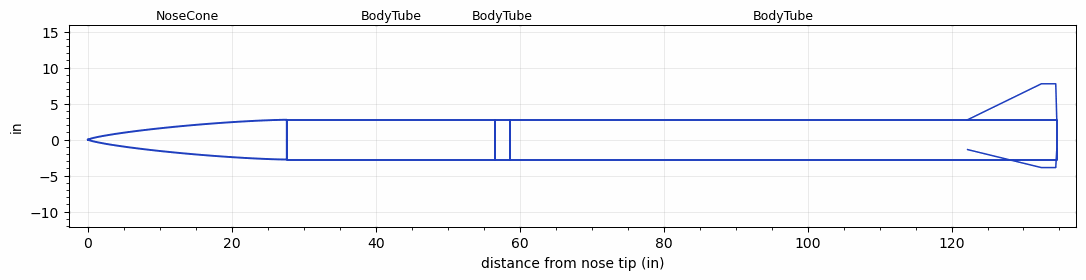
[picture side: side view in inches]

<RASAeroDocument>
 <FileVersion>2</FileVersion>
 <RocketDesign>
  <NoseCone>
   <Length>27.6249</Length>
   <Diameter>5.525</Diameter>
   <Shape>Von Karman Ogive</Shape>
   <Location>0</Location>
  </NoseCone>
  <BodyTube>
   <Length>28.9999</Length>
   <Diameter>5.525</Diameter>
   <Location>27.6249</Location>
  </BodyTube>
  <BodyTube>
   <Length>2</Length>
   <Diameter>5.525</Diameter>
   <Location>56.6249</Location>
  </BodyTube>
  <BodyTube>
   <Length>75.9998</Length>
   <Diameter>5.525</Diameter>
   <Location>58.6249</Location>
   <Fin>
    <Count>3</Count>
    <Chord>12.3937</Chord>
    <Span>5</Span>
    <SweepDistance>10.2515</SweepDistance>
    <TipChord>2</TipChord>
    <Thickness>0.25</Thickness>
    <Location>12.3937</Location>
    <AirfoilSection>Subsonic NACA</AirfoilSection>
   </Fin>
  </BodyTube>
  <Surface>Camouflage Paint</Surface>
  <ModifiedBarrowman>False</ModifiedBarrowman>
  <Turbulence>False</Turbulence>
  <UseBooster1>False</UseBooster1>
  <UseBooster2>False</UseBooster2>
 </RocketDesign>
 <LaunchSite>
  <Altitude>0</Altitude>
  <Pressure>29.9214</Pressure>
  <RodAngle>0</RodAngle>
  <RodLength>3.2808</RodLength>
  <Temperature>59</Temperature>
  <WindSpeed>4.4739</WindSpeed>
 </LaunchSite>
 <Recovery>
  <Altitude1>656.168</Altitude1>
  <Altitude2>1500</Altitude2>
  <DeviceType1>Parachute</DeviceType1>
  <DeviceType2>Parachute</DeviceType2>
  <Event1>True</Event1>
  <Event2>True</Event2>
  <Size1>47.9999</Size1>
  <Size2>119.9998</Size2>
  <EventType1>Apogee</EventType1>
  <EventType2>Altitude</EventType2>
  <CD1>2.2</CD1>
  <CD2>0</CD2>
 </Recovery>
 <SimulationList>
  <Simulation>
   <SustainerEngine>O5500X  (AT)</SustainerEngine>
   <SustainerLaunchWt>65.7</SustainerLaunchWt>
   <SustainerNozzleDiameter>3.5</SustainerNozzleDiameter>
   <SustainerCG>89.63</SustainerCG>
   <SustainerIgnitionDelay>0</SustainerIgnitionDelay>
   <Booster1SeparationDelay>0</Booster1SeparationDelay>
   <Booster1IgnitionDelay>0</Booster1IgnitionDelay>
   <IncludeBooster1>False</IncludeBooster1>
   <Booster2Delay>0</Booster2Delay>
   <IncludeBooster2>False</IncludeBooster2>
   <TimetoApogee>38.50954</TimetoApogee>
   <MaxAltitude>30770.17</MaxAltitude>
   <MaxVelocity>2328.262</MaxVelocity>
  </Simulation>
  <Simulation>
   <SustainerLaunchWt>65.6967</SustainerLaunchWt>
   <SustainerCG>89.6336</SustainerCG>
   <SustainerIgnitionDelay>0</SustainerIgnitionDelay>
   <Booster1SeparationDelay>0</Booster1SeparationDelay>
   <Booster1IgnitionDelay>0</Booster1IgnitionDelay>
   <IncludeBooster1>False</IncludeBooster1>
   <Booster2Delay>0</Booster2Delay>
   <IncludeBooster2>False</IncludeBooster2>
  </Simulation>
  <Simulation>
   <SustainerLaunchWt>64.5888</SustainerLaunchWt>
   <SustainerCG>92.3024</SustainerCG>
   <SustainerIgnitionDelay>0</SustainerIgnitionDelay>
   <Booster1SeparationDelay>0</Booster1SeparationDelay>
   <Booster1IgnitionDelay>0</Booster1IgnitionDelay>
   <IncludeBooster1>False</IncludeBooster1>
   <Booster2Delay>0</Booster2Delay>
   <IncludeBooster2>False</IncludeBooster2>
  </Simulation>
  <Simulation>
   <SustainerLaunchWt>58.0356</SustainerLaunchWt>
   <SustainerCG>92.5564</SustainerCG>
   <SustainerIgnitionDelay>0</SustainerIgnitionDelay>
   <Booster1SeparationDelay>0</Booster1SeparationDelay>
   <Booster1IgnitionDelay>0</Booster1IgnitionDelay>
   <IncludeBooster1>False</IncludeBooster1>
   <Booster2Delay>0</Booster2Delay>
   <IncludeBooster2>False</IncludeBooster2>
  </Simulation>
  <Simulation>
   <SustainerLaunchWt>65.6967</SustainerLaunchWt>
   <SustainerCG>89.6336</SustainerCG>
   <SustainerIgnitionDelay>0</SustainerIgnitionDelay>
   <Booster1SeparationDelay>0</Booster1SeparationDelay>
   <Booster1IgnitionDelay>0</Booster1IgnitionDelay>
   <IncludeBooster1>False</IncludeBooster1>
   <Booster2Delay>0</Booster2Delay>
   <IncludeBooster2>False</IncludeBooster2>
  </Simulation>
 </SimulationList>
</RASAeroDocument>
